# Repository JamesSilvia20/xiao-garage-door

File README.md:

# XIAO Garage Door 🚗🏠

**Make your garage door opener smart for about $10 in parts.** This is a tiny open-source board that holds a [Seeed Studio XIAO ESP32-C6](https://www.seeedstudio.com/Seeed-Studio-XIAO-ESP32C6-p-5884.html) and wires to your opener's wall-button terminals. You can then open and close your garage from **Home Assistant**, **Apple Home** (with Siri and automations), or anything else that talks to [ESPHome](https://esphome.io).

No cloud, no subscription, no app from the opener company. Everything runs on your own network.

## What it does

| Your opener | What you get |
|---|---|
| **Security+ 2.0** (LiftMaster / Chamberlain / Craftsman with a **yellow** learn button, the myQ kind) | Real open / closed / opening / closing status, light, lock, obstruction alerts and motion, read straight from the opener. |
| **Security+ 1.0** (same brands, **purple / red / orange** learn button) | Same as above. |
| **Any opener with a simple 2-wire wall button** (most other brands, older units) | Open / close / stop from your phone. Add a $5 magnetic reed switch for true open/closed status. |

One board does all of these. You pick the matching firmware.

## Start here 👇

New to this? Follow the guides in order. They're written for complete beginners, and we explain every step.

1. 🔍 [**Which opener do I have?**](docs/start/which-opener.md): pick your firmware in 2 minutes.
2. 🛒 [**Parts and cost**](docs/start/parts.md): everything you need, with links.
3. ⚠️ [**Safety first**](docs/start/safety.md): please read this one.
4. 🔧 Get the hardware, either way:
   - [**Order the ready-made PCB**](docs/hardware/order-pcb.md) from JLCPCB or PCBWay, all parts soldered for you, about $25–40 for 5 boards; **or**
   - [**Build it on perfboard**](docs/hardware/perfboard.md) with a few cheap parts (new to soldering? see [**Soldering 101**](docs/hardware/soldering-101.md)).
5. ⚡ [**Flash the firmware**](docs/setup/flash.md): straight from your web browser, no software to install.
6. 🏠 [**Add to Home Assistant**](docs/setup/home-assistant.md) and [**Apple Home**](docs/setup/apple-home.md).
7. 🪛 [**Install it at the opener**](docs/setup/install.md).

Stuck? See [**Troubleshooting**](docs/help/troubleshooting.md) and the [**FAQ**](docs/help/faq.md).

> [!TIP]
> Prefer a website? The same guides are at **https://jamessilvia20.github.io/xiao-garage-door/**, and that's where the one-click **browser installer** lives.

## What's in this repo

```
firmware/        ESPHome configs (one per opener type) - flash from the browser or adopt in ESPHome
hardware/pcb/    The PCB: KiCad board, scripts that build it, and ready-to-upload JLCPCB / PCBWay files
docs/            All the tutorials (this is also the website)
```

## Project status

Honest status, so you know what's been tested:

| Part | Status |
|---|---|
| Dry-contact firmware + hand-built perfboard | ✅ Built and bench-tested by the author (switches the wall-button contacts on command, shows up in HA and Apple Home). |
| Security+ 2.0 / 1.0 firmware | ✅ Compiles for the XIAO C6, using the proven [esphome-ratgdo](https://github.com/ratgdo/esphome-ratgdo) component and the community [rat-ratgdo](https://github.com/Kaldek/rat-ratgdo) circuit. 🧪 Not yet tested by the author on this exact board. Reports welcome! |
| PCB v1 | 🧪 Design passes KiCad DRC with 0 errors, and the JLCPCB/PCBWay files are generated. First boards are on order. |

Built one? Please open an issue or discussion with how it went (photos welcome!), so we can turn the 🧪s into ✅s.

## Credits

This stands on the shoulders of [**ratgdo**](https://github.com/ratgdo) (Paul Wieland and contributors), [**rat-ratgdo**](https://github.com/Kaldek/rat-ratgdo), [**esphome-ratgdo**](https://github.com/ratgdo/esphome-ratgdo), [**ESPHome**](https://esphome.io) and [**Home Assistant**](https://www.home-assistant.io). If you want a polished, ready-made product, buy an official [ratgdo](https://ratcloud.llc). It's great and supports the people who figured all this out.

See [Credits and license](docs/makers/credits.md).

## License

[MIT](LICENSE) for everything in this repo (firmware configs, PCB, docs). The Security+ firmware pulls in esphome-ratgdo, which is GPL-2.0.

> [!WARNING]
> Garage doors are heavy and can hurt people. Keep your photo-eye safety sensors connected and working. Never close the door remotely unless you can be sure nobody is under it. See [Safety first](docs/start/safety.md).

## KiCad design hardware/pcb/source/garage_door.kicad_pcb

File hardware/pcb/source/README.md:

# PCB source

Generated with KiCad 10's Python API and autorouted with freerouting. See [Edit the PCB](../../../docs/makers/edit-pcb.md) for how to rebuild.

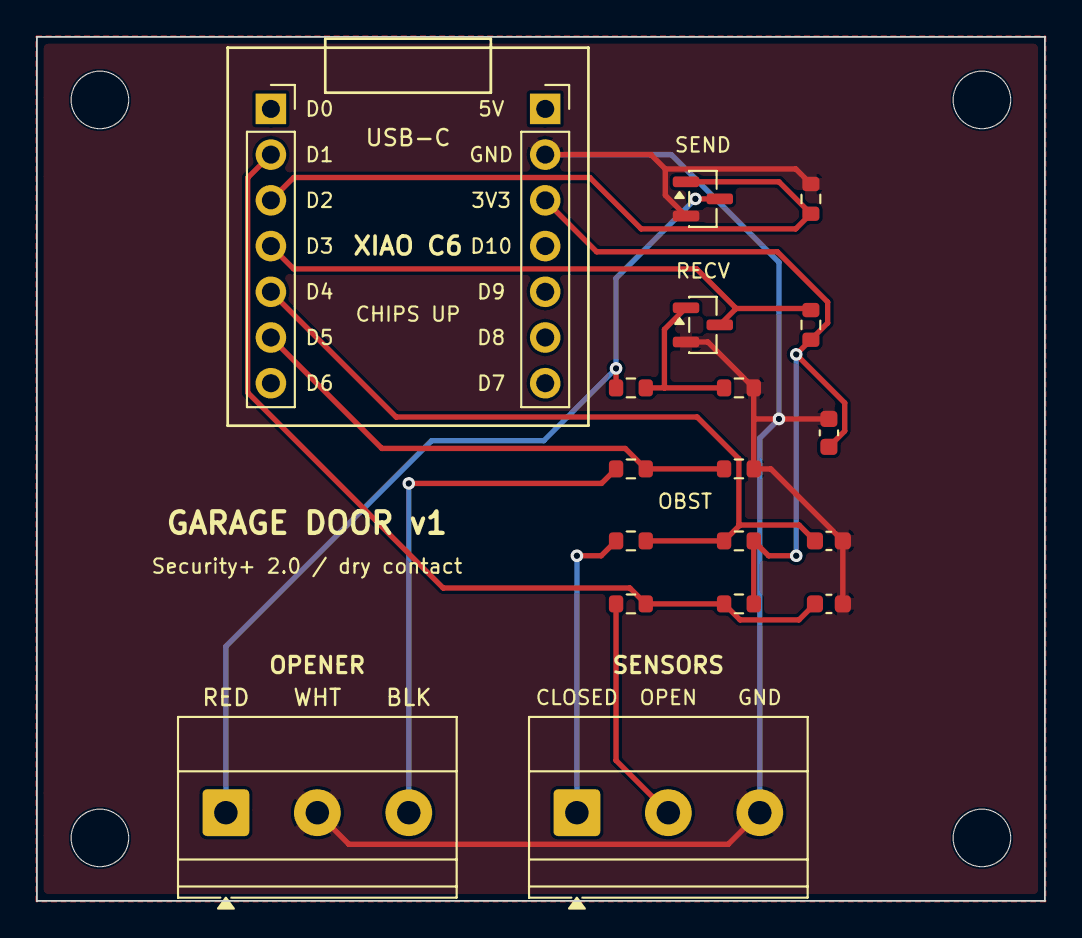
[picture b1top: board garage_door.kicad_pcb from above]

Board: 2 copper layers, 56.0 x 48.0 mm, 23 parts (0 on the bottom side), 12 nets.

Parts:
C1, C2, C3: 100nF; C_0603_1608Metric
H1, H2, H3, H4: M3; MountingHole_3.2mm_M3
J1: OPENER; TerminalBlock_Phoenix_MKDS-1,5-3-5.08_1x03_P5.08mm_Horizont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
J2: SENSORS; TerminalBlock_Phoenix_MKDS-1,5-3-5.08_1x03_P5.08mm_Horizont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
J3: XIAO L; PinSocket_1x07_P2.54mm_Vertical
J4: XIAO R; PinSocket_1x07_P2.54mm_Vertical
Q1: AO3400A; SOT-23
Q2: 2N7002; SOT-23
R1, R2, R5, R6, R7, R8: 10k; R_0603_1608Metric
R3, R9, R10: 1k; R_0603_1608Metric
R4: 100k; R_0603_1608Metric

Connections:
+3V3: C3.1, J4.3, R2.1, R7.2, R8.2
BLACK: J1.3, R5.1
CLOSED: J2.1, R9.1
CLOSED_IN: C1.1, J3.5, R7.1, R9.2
GND: C1.2, C2.2, C3.2, J1.2, J2.3, J4.2, Q1.2, Q2.2, R1.2, R4.2, R6.2
OBST: J3.6, R5.2, R6.1
OPEN: J2.2, R10.1
OPEN_IN: C2.1, J3.2, R8.1, R10.2
RED: J1.1, Q1.3, R3.1
RX: J3.4, Q2.3, R2.2
RX_G: Q2.1, R3.2, R4.1
TX: J3.3, Q1.1, R1.1

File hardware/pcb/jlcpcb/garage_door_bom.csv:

Comment,Designator,Footprint,LCSC Part #
100nF,"C1,C2,C3",C_0603_1608Metric,C14663
OPENER,J1,"TerminalBlock_Phoenix_MKDS-1,5-3-5.08_1x03_P5.08mm_Horizontal",C474953
SENSORS,J2,"TerminalBlock_Phoenix_MKDS-1,5-3-5.08_1x03_P5.08mm_Horizontal",C474953
XIAO L,J3,PinSocket_1x07_P2.54mm_Vertical,C2932672
XIAO R,J4,PinSocket_1x07_P2.54mm_Vertical,C2932672
AO3400A,Q1,SOT-23,C20917
2N7002,Q2,SOT-23,C8545
10k,"R1,R2,R5,R6,R7,R8",R_0603_1608Metric,C25804
1k,"R3,R9,R10",R_0603_1608Metric,C21190
100k,R4,R_0603_1608Metric,C25803

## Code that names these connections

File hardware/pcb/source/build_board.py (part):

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XIAO pins (same as the hand-built boards):
  D2 GPIO2  -> Q1 AO3400A gate (send / press), R1 10k gate pull-down
  D3 GPIO21 <- Q2 2N7002 drain (receive, inverted), R2 10k pull-up; gate <- RED via R3 1k, R4 100k pull-down
  D5 GPIO23 <- BLACK via R5/R6 10k/10k divider (obstruction)
  D4 GPIO22 <- CLOSED via R9 1k, R7 10k pull-up, C1 100nF
  D1 GPIO1  <- OPEN   via R10 1k, R8 10k pull-up, C2 100nF

Run with KiCad's Python:  build_board.py  ->  garage_door.kicad_pcb (unrouted; see route.sh)
Coordinates in mm, KiCad frame (x right, y down). USB-C of the XIAO points to the top edge.
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right = ['5V', 'GND', '3V3', 'D10', 'D9', 'D8', 'D7']
J3 = place('Connector_PinSocket_2.54mm', 'PinSocket_1x07_P2.54mm_Vertical', 'J3', 'XIAO L', XL, Y0, lcsc='C2932672')
J4 = place('Connector_PinSocket_2.54mm', 'PinSocket_1x07_P2.54mm_Vertical', 'J4', 'XIAO R', XR, Y0, lcsc='C2932672')
pin_net = {'D1': 'OPEN_IN', 'D2': 'TX', 'D3': 'RX', 'D4': 'CLOSED_IN', 'D5': 'OBST', 'GND': 'GND', '3V3': '+3V3'}
for i, n in enumerate(left):
    if n in pin_net:
        connect(J3, i + 1, pin_net[n])
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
